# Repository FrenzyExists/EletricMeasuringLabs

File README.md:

# Board files

All files containing development of the pika-board, a macro keyboard I've been doing from time to time

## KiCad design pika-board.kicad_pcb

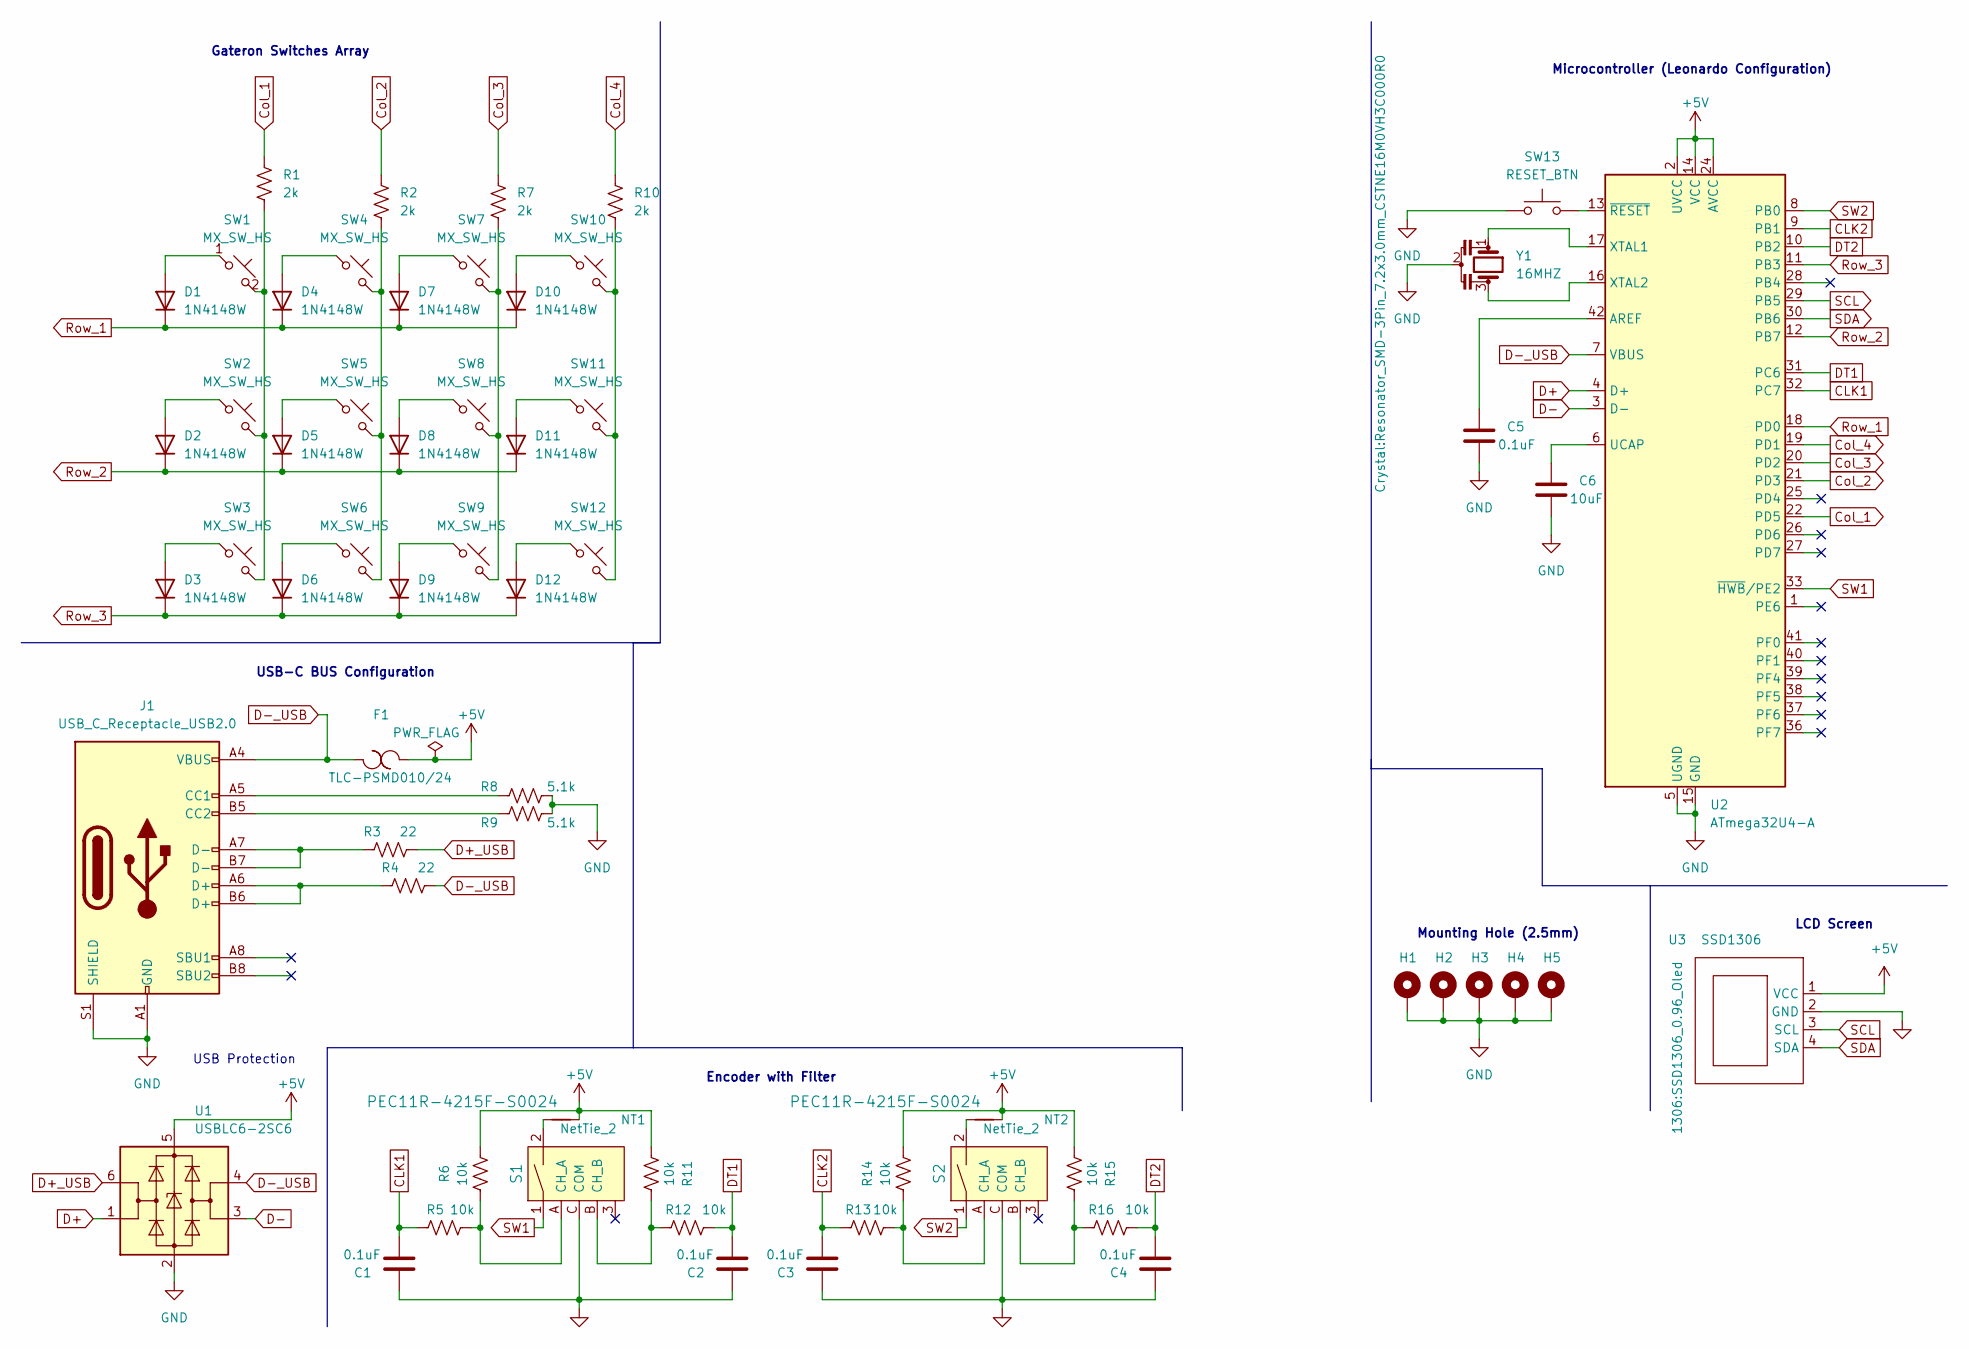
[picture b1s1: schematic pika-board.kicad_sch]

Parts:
C1, C2, C3, C4, C5: 0.1uF; C_0805_2012Metric; LCSC Part # C126469
C6: 10uF; C_0805_2012Metric; LCSC Part # C90544
D1, D2, D3, D4, D5, D6, D7, D8, D9, D10, D11, D12: 1N4148W; D_SOD-123; LCSC Part # C2892570
F1: TLC-PSMD010/24; Fuse_0805_2012Metric_Pad1.15x1.40mm_HandSolder; LCSC Part # C261938
H1, H2, H3, H4, H5: MountingHole_Pad; MountingHole_2.5mm_Pad_Via
J1: USB_C_Receptacle_USB2.0; USB_C_Receptacle_XKB_U262-16XN-4BVC11; LCSC Part # C319148
NT1, NT2: NetTie_2; NetTie-2_SMD_Pad2.0mm
R1, R2, R7, R10: 2k; R_0805_2012Metric; LCSC Part # C114748
R3, R4: 22; R_0805_2012Metric; LCSC Part # C409739
R5, R6, R11, R12, R13, R14, R15, R16: 10k; R_0805_2012Metric; LCSC Part # C115295
R8, R9: 5.1k; R_0805_2012Metric; LCSC Part # C269748
S1, S2: PEC11R-4215F-S0024; Rotary_Encoder_Switched_PEC11R; MPN PEC11R-4215F-S0024; Digi-Key_PN PEC11R-4215F-S0024-ND
SW1, SW2, SW3, SW4, SW5, SW6, SW7, SW8, SW9, SW10, SW11, SW12: MX_SW_HS; SW_MX_HS_1u
SW13: RESET_BTN; SW_Push_1P1T_NO_6x6mm_H9.5mm; LCSC Part # C178262
U1: USBLC6-2SC6; SOT-23-6; LCSC Part # C7519
U2: ATmega32U4-A; TQFP-44_10x10mm_P0.8mm; LCSC Part # C44854
U3: SSD1306; SSD1306_0.96_Oled
Y1: 16MHZ; Resonator_SMD-3Pin_7.2x3.0mm_CSTNE16M0VH3C000R0; LCSC Part # C882605

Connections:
+5V: F1.2, NT1.2, NT2.2, R6.2, R11.1, R14.2, R15.1, U1.5 (VBUS), U2.2 (UVCC), U2.14 (VCC), U2.24 (AVCC), U2.34 (VCC), U2.44 (AVCC), U3.1 (VCC)
CLK1: C1.2, R5.1, U2.32 (PC7)
CLK2: C3.2, R13.1, U2.9 (PB1)
Col_1: R1.1, U2.22 (PD5)
Col_2: R2.1, U2.21 (PD3)
Col_3: R7.1, U2.20 (PD2)
Col_4: R10.1, U2.19 (PD1)
D+: U1.1 (I/O1), U2.4 (D+)
D+_USB: R3.2, U1.6 (I/O1)
D-: U1.3 (I/O2), U2.3 (D-)
D-_USB: F1.1, J1.A4 (VBUS), J1.A9 (VBUS), J1.B4 (VBUS), J1.B9 (VBUS), R4.2, U1.4 (I/O2), U2.7 (VBUS)
DT1: C2.2, R12.2, U2.31 (PC6)
DT2: C4.2, R16.2, U2.10 (PB2)
GND: C1.1, C2.1, C3.1, C4.1, C5.2, C6.2, H1.1, H2.1, H3.1, H4.1, H5.1, J1.A1 (GND), J1.A12 (GND), J1.B1 (GND), J1.B12 (GND), J1.S1 (SHIELD), R8.2, R9.2, S1.C (COM), S2.C (COM), SW13.1, U1.2 (GND), U2.5 (UGND), U2.15 (GND), U2.23 (GND), U2.35 (GND), U2.43 (GND), U3.2 (GND), Y1.2
unnamed: C5.1, U2.42 (AREF)
unnamed: C6.1, U2.6 (UCAP)
unnamed: D1.2 (A), SW1.1
unnamed: D2.2 (A), SW2.1
unnamed: D3.2 (A), SW3.1
unnamed: D4.2 (A), SW4.1
unnamed: D5.2 (A), SW5.1
unnamed: D6.2 (A), SW6.1
unnamed: D7.2 (A), SW7.1
unnamed: D8.2 (A), SW8.1
unnamed: D9.2 (A), SW9.1
unnamed: D10.2 (A), SW10.1
unnamed: D11.2 (A), SW11.1
unnamed: D12.2 (A), SW12.1
unnamed: J1.A5 (CC1), R8.1
unnamed: J1.A6 (D+), J1.B6 (D+), R4.1
unnamed: J1.A7 (D-), J1.B7 (D-), R3.1
unnamed: J1.B5 (CC2), R9.1
unnamed: NT1.1, S1.2
unnamed: NT2.1, S2.2
unnamed: R1.2, SW1.2, SW2.2, SW3.2
unnamed: R2.2, SW4.2, SW5.2, SW6.2
unnamed: R5.2, R6.1, S1.A (CH_A)
unnamed: R7.2, SW7.2, SW8.2, SW9.2
unnamed: R10.2, SW10.2, SW11.2, SW12.2
unnamed: R11.2, R12.1, S1.B (CH_B)
unnamed: R13.2, R14.1, S2.A (CH_A)
unnamed: R15.2, R16.1, S2.B (CH_B)
unnamed: SW13.2, U2.13 (~RESET)
unnamed: U2.16 (XTAL2), Y1.3
unnamed: U2.17 (XTAL1), Y1.1
Row_1: D1.1 (K), D4.1 (K), D7.1 (K), D10.1 (K), U2.18 (PD0)
Row_2: D2.1 (K), D5.1 (K), D8.1 (K), D11.1 (K), U2.12 (PB7)
Row_3: D3.1 (K), D6.1 (K), D9.1 (K), D12.1 (K), U2.11 (PB3)
SCL: U2.29 (PB5), U3.3 (SCL)
SDA: U2.30 (PB6), U3.4 (SDA)
SW1: S1.1, U2.33 (~HWB/PE2)
SW2: S2.1, U2.8 (PB0)

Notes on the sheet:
Encoder with Filter
Mounting Hole (2.5mm)
LCD Screen
USB Protection
Gateron Switches Array
Microcontroller (Leonardo Configuration)
USB-C BUS Configuration

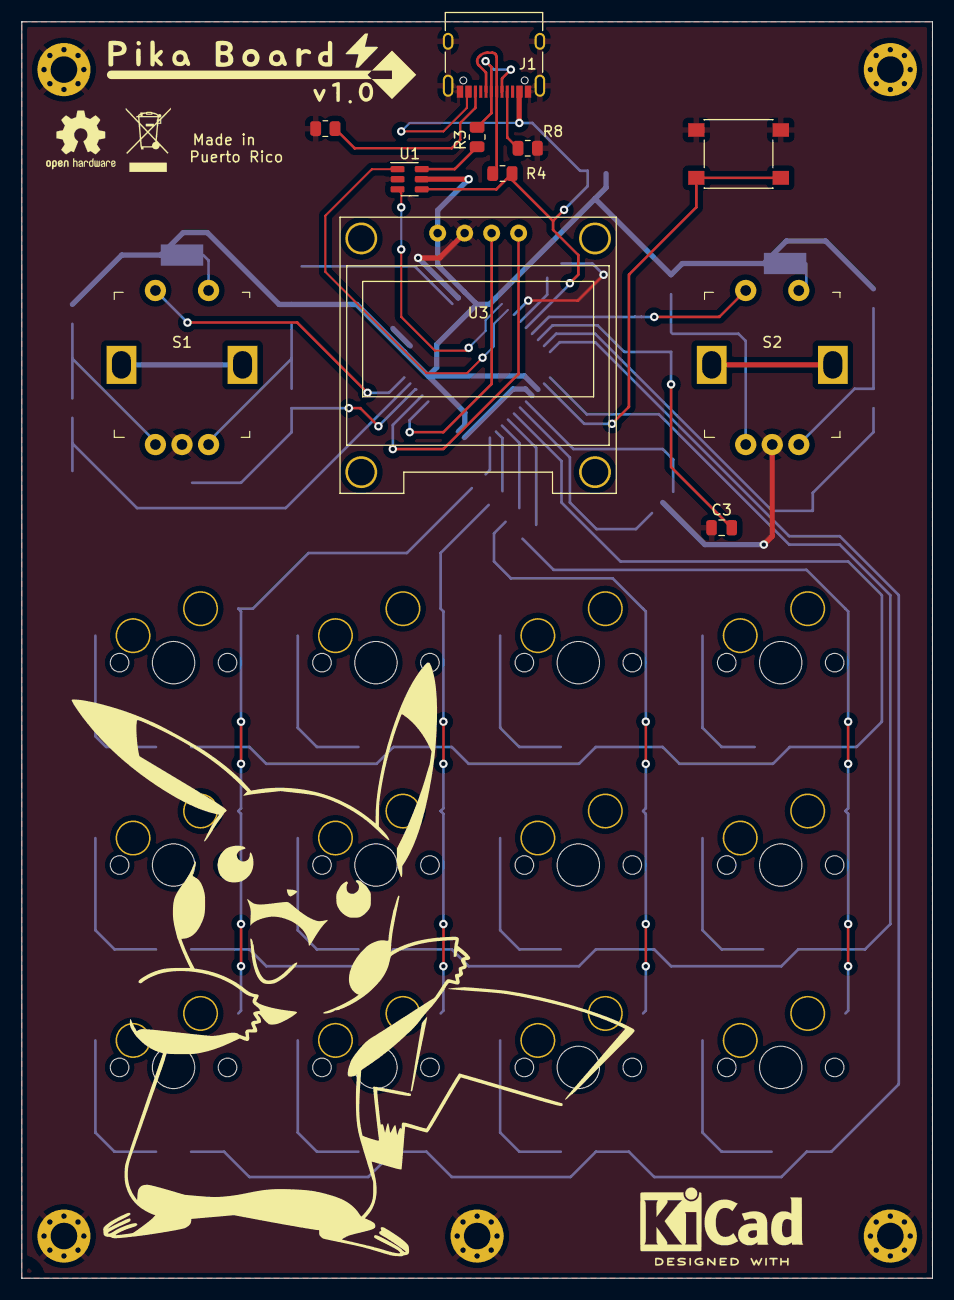
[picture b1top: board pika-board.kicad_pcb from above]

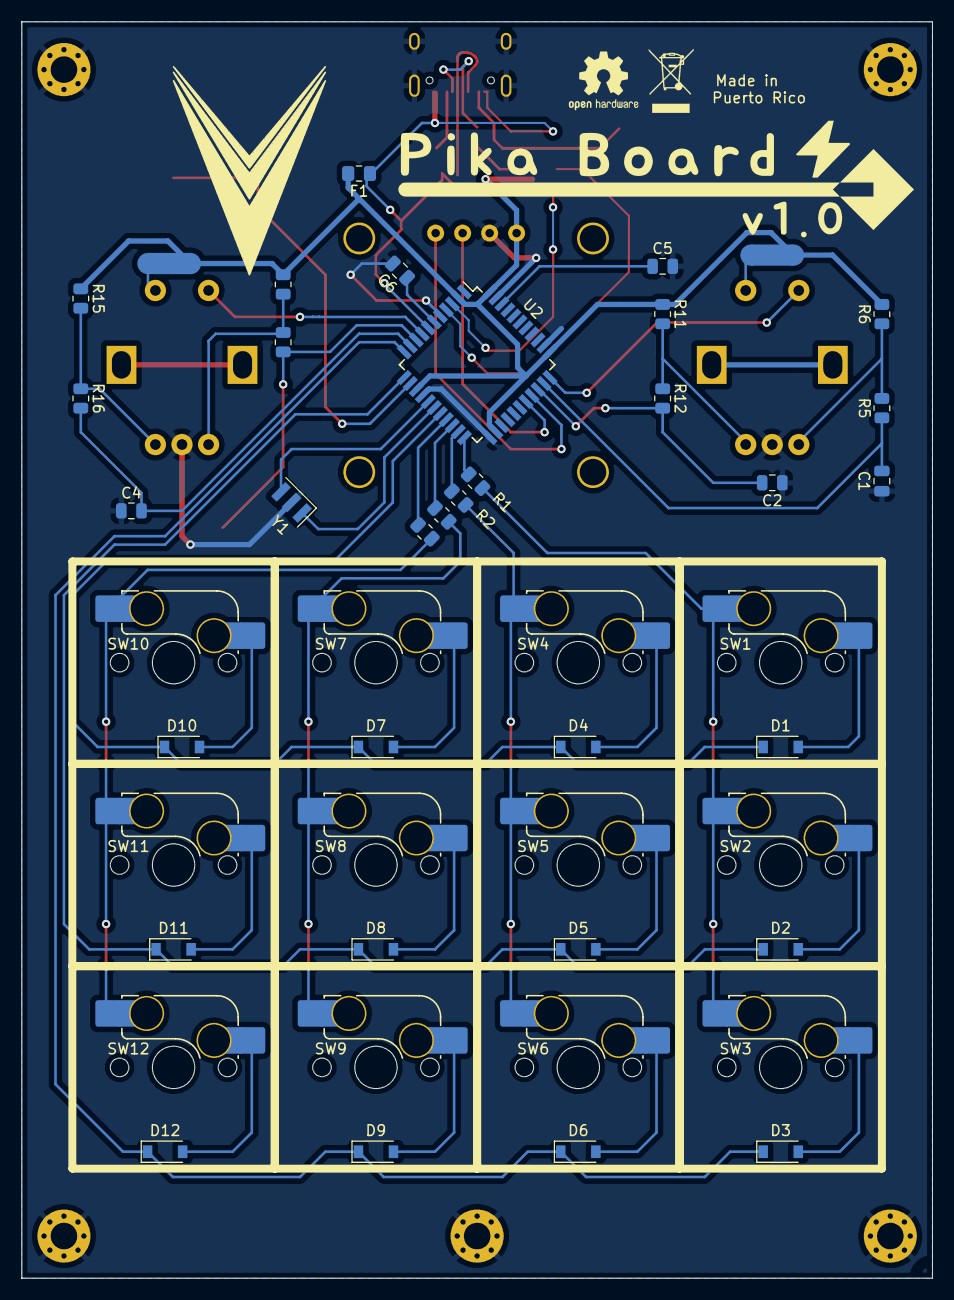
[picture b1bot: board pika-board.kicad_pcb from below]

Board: 2 copper layers, 85.7 x 118.3 mm, 62 parts (46 on the bottom side), 52 nets.

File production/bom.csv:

Designator,Footprint,Quantity,Value,LCSC Part #
"C1, C2, C3, C4, C5",C_0805_2012Metric,5,0.1uF,C126469
C6,C_0805_2012Metric,1,10uF,C90544
"D1, D10, D11, D12, D2, D3, D4, D5, D6, D7, D8, D9",D_SOD-123,12,1N4148W,C2892570
F1,Fuse_0805_2012Metric_Pad1.15x1.40mm_HandSolder,1,TLC-PSMD010/24,C261938
"H1, H2, H3, H4, H5",MountingHole_2.5mm_Pad_Via,5,MountingHole_Pad,NULL
J1,USB_C_Receptacle_XKB_U262-16XN-4BVC11,1,USB_C_Receptacle_USB2.0,C319148
"R1, R10, R2, R7",R_0805_2012Metric,4,2k,C114748
"R11, R12, R13, R14, R15, R16, R5, R6",R_0805_2012Metric,8,10k,C115295
"R3, R4",R_0805_2012Metric,2,22,C409739
"R8, R9",R_0805_2012Metric,2,5.1k,C269748
"S1, S2",Rotary_Encoder_Switched_PEC11R,2,PEC11R-4215F-S0024,C143790
"SW1, SW10, SW11, SW12, SW2, SW3, SW4, SW5, SW6, SW7, SW8, SW9",SW_MX_HS_1u,12,MX_SW_HS,NULL
SW13,SW_Push_1P1T_NO_6x6mm_H9.5mm,1,RESET_BTN,C178262
U1,SOT-23-6,1,USBLC6-2SC6,C7519
U2,TQFP-44_10x10mm_P0.8mm,1,ATmega32U4-A,C44854
U3,SSD1306_0.96_Oled,1,SSD1306,NULL
Y1,Resonator_SMD-3Pin_7.2x3.0mm_CSTNE16M0VH3C000R0,1,16MHZ,C882605

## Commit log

2021-06-04 Exp 1 - Just Testing
2021-06-04 added a guide cuz I'm lost
2021-06-06 Y E S
2021-06-06 Finished Max Values
2021-06-06 Almost forgot this
2021-06-06 Answered a question
2022-12-05 REBORN
